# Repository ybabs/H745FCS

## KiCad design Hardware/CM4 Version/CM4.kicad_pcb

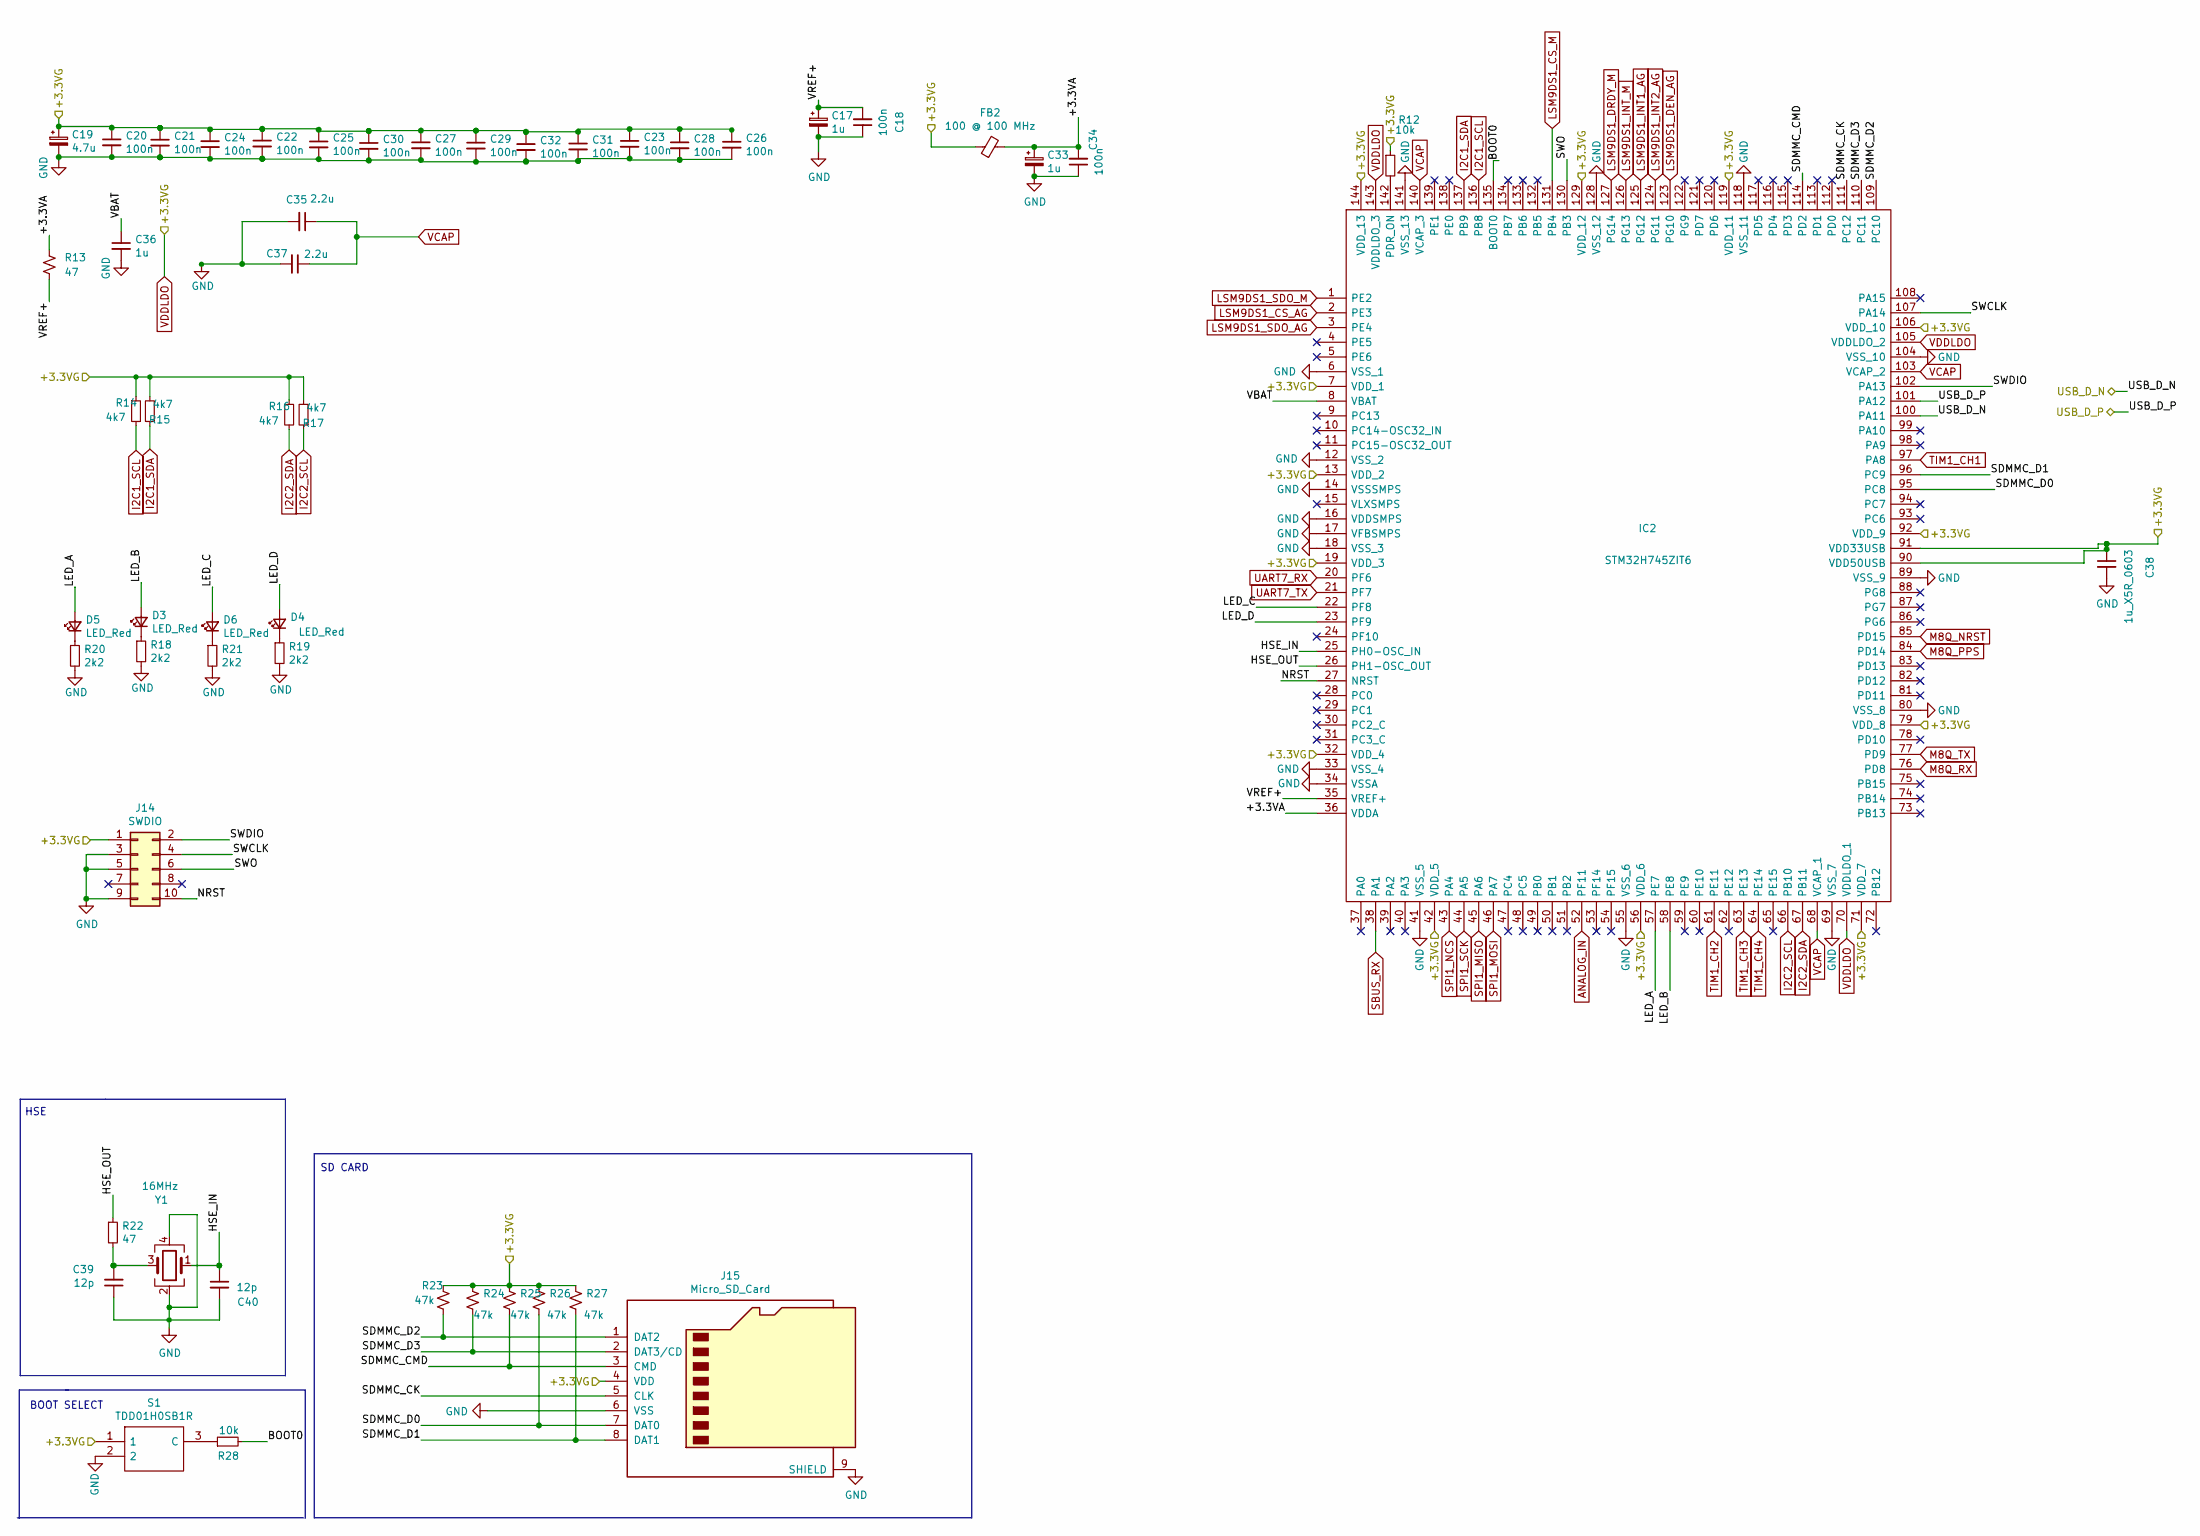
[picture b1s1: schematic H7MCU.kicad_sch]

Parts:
C17, C33: 1u; CP_EIA-3216-18_Kemet-A; Manufacturer_Part_Number TAJA105M016RNJ; LCSC Part # C7176
C18, C20, C21, C22, C23, C24, C25, C26, C27, C28, C29, C30, C31, C32, C34: 100n; C_0402_1005Metric; Digi-Key_PN 587-1226-2-ND
C19: 4.7u; CP_EIA-3216-18_Kemet-A; LCSC Part # C129235
C35, C37: 2.2u; C_0603_1608Metric; LCSC Part # C19666
C36: 1u; C_0402_1005Metric; Digi-Key_PN 587-1226-2-ND
C38: 1u_X5R_0603; C_0603_1608Metric; LCSC Part # C15849
C39, C40: 12p; C_0402_1005Metric; LCSC Part # C1547
D3, D4, D5, D6: LED_Red; LED_0603_1608Metric; LCSC Part # C72043
FB2: 100 @ 100 MHz; L_0603_1608Metric; Manufacturer_Part_Number MPZ1608S101ATAH0
IC2: STM32H745ZIT6; QFP50P2200X2200X160-144N; Manufacturer_Part_Number STM32H745ZIT6; Mouser Part Number 511-STM32H745ZIT6
J14: SWDIO; PinHeader_2x05_P1.27mm_Vertical
J15: Micro_SD_Card; microSD_HC_Hirose_DM3AT-SF-PEJM5; Manufacturer_Part_Number DM3AT-SF-PEJM5
R12, R28: 10k; R_0402_1005Metric; Digi-Key_PN RG10P10.0KDTR-ND
R13, R22: 47; R_0402_1005Metric; LCSC Part # C23182
R14, R15, R16, R17: 4k7; R_0402_1005Metric; LCSC Part # C23162
R18, R19, R20, R21: 2k2; R_0603_1608Metric; LCSC Part # C4190
R23, R24, R25, R26, R27: 47k; R_0402_1005Metric; Digi-Key_PN P47KDCTR-ND
S1: TDD01H0SB1R; SOT175P420X230-3N; Manufacturer_Part_Number TDD01H0SB1R; Mouser Part Number 611-TDD01H0SB1R
Y1: 16MHz; Crystal_SMD_3225-4Pin_3.2x2.5mm; Manufacturer_Part_Number X322516MLB4SI; LCSC Part # C13738

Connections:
/MCU/+3.3VA: C33.1, C34.2, FB2.2, IC2.36 (VDDA), R13.2
/MCU/BOOT0: IC2.135 (BOOT0), R28.2
/MCU/HSE_IN: C40.1, IC2.25 (PH0-OSC_IN), Y1.1
/MCU/HSE_OUT: IC2.26 (PH1-OSC_OUT), R22.1
/MCU/LED_A: D5.2 (A), IC2.57 (PE7)
/MCU/LED_B: D3.2 (A), IC2.58 (PE8)
/MCU/LED_C: D6.2 (A), IC2.22 (PF8)
/MCU/LED_D: D4.2 (A), IC2.23 (PF9)
/MCU/NRST: IC2.27 (NRST), J14.10
/MCU/SDMMC_CK: IC2.111 (PC12), J15.5 (CLK)
/MCU/SDMMC_CMD: IC2.114 (PD2), J15.3 (CMD), R25.1
/MCU/SDMMC_D0: IC2.95 (PC8), J15.7 (DAT0), R26.1
/MCU/SDMMC_D1: IC2.96 (PC9), J15.8 (DAT1), R27.1
/MCU/SDMMC_D2: IC2.109 (PC10), J15.1 (DAT2), R23.1
/MCU/SDMMC_D3: IC2.110 (PC11), J15.2 (DAT3/CD), R24.1
/MCU/SWCLK: IC2.107 (PA14), J14.4
/MCU/SWDIO: IC2.102 (PA13), J14.2
/MCU/SWO: IC2.130 (PB3), J14.6
/MCU/VBAT: C36.1, IC2.8 (VBAT)
/MCU/VREF+: C17.1, C18.2, IC2.35 (VREF+), R13.1
GND: C17.2, C18.1, C19.2, C20.2, C21.2, C22.2, C23.2, C24.2, C25.2, C26.2, C27.2, C28.2, C29.2, C30.2, C31.2, C32.2, C33.2, C34.1, C35.2, C36.2, C37.2, C38.2, C39.1, C40.2, IC2.6 (VSS_1), IC2.12 (VSS_2), IC2.14 (VSSSMPS), IC2.16 (VDDSMPS), IC2.17 (VFBSMPS), IC2.18 (VSS_3), IC2.33 (VSS_4), IC2.34 (VSSA), IC2.41 (VSS_5), IC2.55 (VSS_6), IC2.69 (VSS_7), IC2.80 (VSS_8), IC2.89 (VSS_9), IC2.104 (VSS_10), IC2.118 (VSS_11), IC2.128 (VSS_12), IC2.141 (VSS_13), J14.3, J14.5, J14.9, J15.6 (VSS), J15.9 (SHIELD), R18.2, R19.2, R20.2, R21.2, S1.2, Y1.2, Y1.4; also elsewhere on the board
I2C1_SCL: IC2.136 (PB8), R14.2; also elsewhere on the board
I2C1_SDA: IC2.137 (PB9), R15.1; also elsewhere on the board
I2C2_SCL: IC2.66 (PB10), R17.1; also elsewhere on the board
I2C2_SDA: IC2.67 (PB11), R16.2; also elsewhere on the board
unnamed: C39.2, R22.2, Y1.3
unnamed: D3.1 (K), R18.1
unnamed: D4.1 (K), R19.1
unnamed: D5.1 (K), R20.1
unnamed: D6.1 (K), R21.1
unnamed: IC2.142 (PDR_ON), R12.2
unnamed: R28.1, S1.3 (C)
VCAP: C35.1, C37.1, IC2.68 (VCAP_1), IC2.103 (VCAP_2), IC2.140 (VCAP_3)
VDDLDO: C19.1, C20.1, C21.1, C22.1, C23.1, C24.1, C25.1, C26.1, C27.1, C28.1, C29.1, C30.1, C31.1, C32.1, C38.1, FB2.1, IC2.7 (VDD_1), IC2.13 (VDD_2), IC2.19 (VDD_3), IC2.32 (VDD_4), IC2.42 (VDD_5), IC2.56 (VDD_6), IC2.70 (VDDLDO_1), IC2.71 (VDD_7), IC2.79 (VDD_8), IC2.90 (VDD50USB), IC2.91 (VDD33USB), IC2.92 (VDD_9), IC2.105 (VDDLDO_2), IC2.106 (VDD_10), IC2.119 (VDD_11), IC2.129 (VDD_12), IC2.143 (VDDLDO_3), IC2.144 (VDD_13), J14.1, J15.4 (VDD), R12.1, R14.1, R15.2, R16.1, R17.2, R23.2, R24.2, R25.2, R26.2, R27.2, S1.1; also elsewhere on the board

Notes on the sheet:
SD CARD
HSE
BOOT SELECT

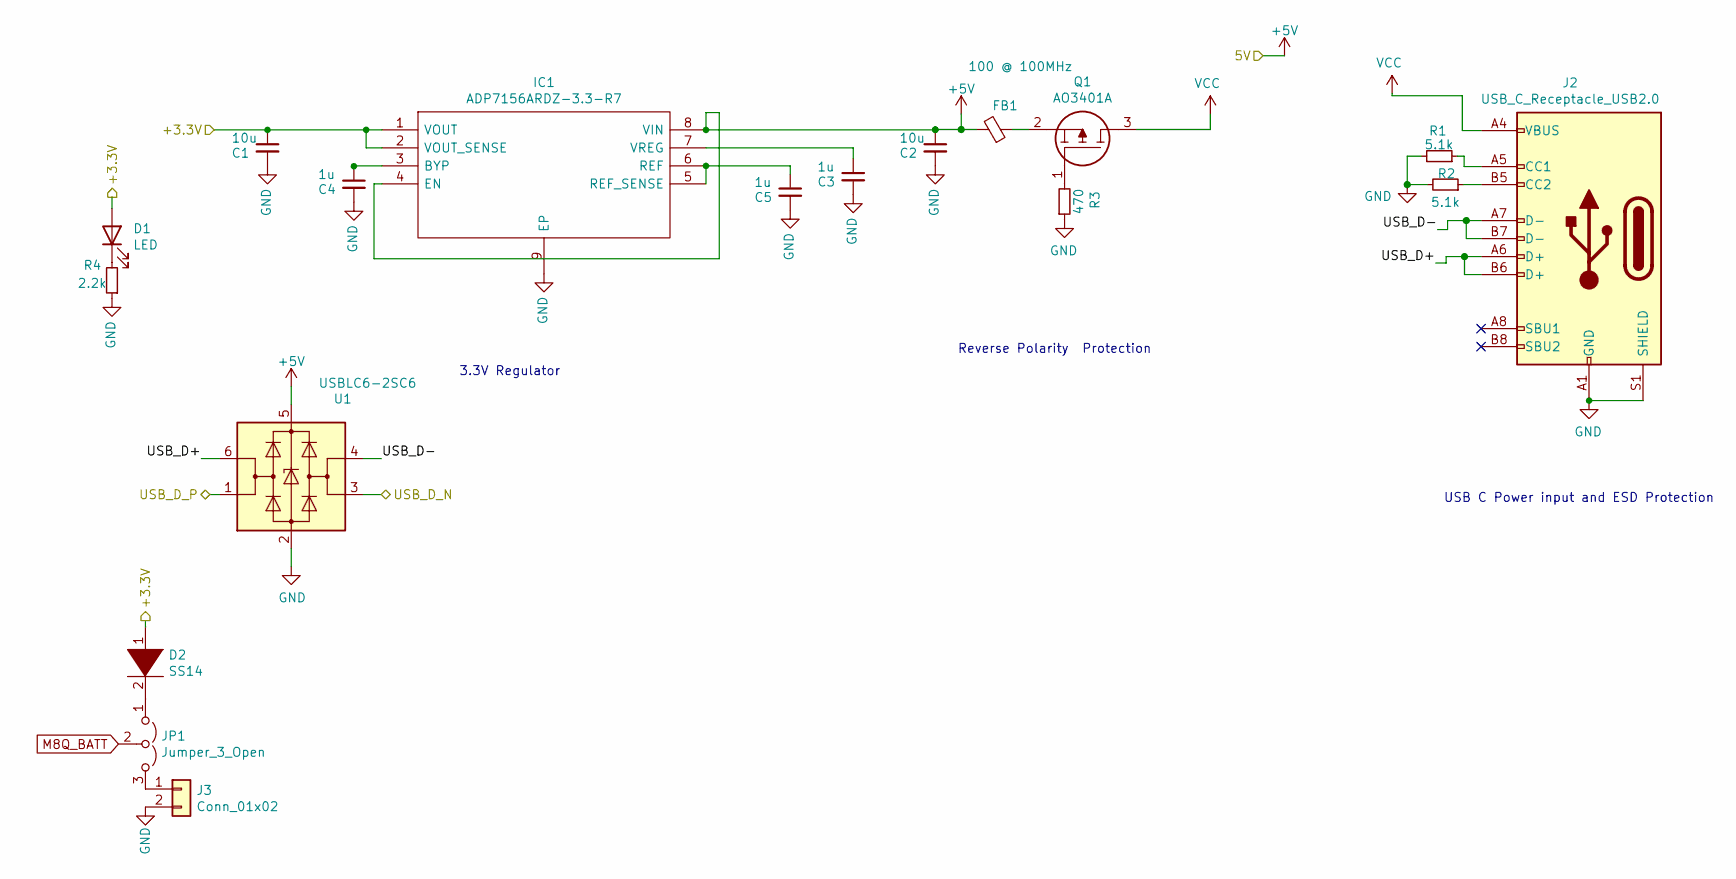
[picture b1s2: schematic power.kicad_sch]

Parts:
C1, C2: 10u; C_0603_1608Metric; LCSC Part # C19702
C3, C4, C5: 1u; C_0603_1608Metric; LCSC Part # C15849
D1: LED; LED_0603_1608Metric; LCSC Part # C72043
D2: SS14; D_SMA; LCSC Part # C111631
FB1: 100 @ 100MHz; L_0603_1608Metric; Manufacturer_Part_Number BLM21PG600SH1D
IC1: ADP7156ARDZ-3.3-R7; SOIC127P600X175-9N; Manufacturer_Part_Number ADP7156ARDZ-3.3-R7; Mouser Part Number 584-ADP7156ARDZ3.3R7
J2: USB_C_Receptacle_USB2.0; USB_C_Receptacle_HRO_TYPE-C-31-M-12; Manufacturer_Part_Number TYPE-C-31-M-12; LCSC Part # C165948
J3: Conn_01x02; Molex_PicoBlade_53261-0271_1x02-1MP_P1.25mm_Horizontal; Manufacturer_Part_Number 0532610271; Digi-Key_PN WM7620TR-ND
JP1: Jumper_3_Open; SolderJumper-3_P1.3mm_Open_RoundedPad1.0x1.5mm
Q1: AO3401A; SOT95P280X125-3N; Manufacturer_Part_Number AO3401A
R1, R2: 5.1k; R_1206_3216Metric; LCSC Part # C26033
R3: 470; R_1206_3216Metric; LCSC Part # C26033
R4: 2.2k; R_0603_1608Metric; LCSC Part # C4190
U1: USBLC6-2SC6; SOT-23-6; Manufacturer_Part_Number USBLC6-2SC6; LCSC Part # C7519

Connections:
+5V: C2.1, FB1.2, IC1.4 (EN), IC1.8 (VIN), U1.5 (VBUS); also elsewhere on the board
/Power/USB_D+: J2.A6 (D+), J2.B6 (D+), U1.6 (I/O1)
/Power/USB_D-: J2.A7 (D-), J2.B7 (D-), U1.4 (I/O2)
/Power/USB_D_N: U1.3 (I/O2)
/Power/USB_D_P: U1.1 (I/O1)
GND: C1.2, C2.2, C3.2, C4.2, C5.2, IC1.9 (EP), J2.A1 (GND), J2.A12 (GND), J2.B1 (GND), J2.B12 (GND), J2.S1 (SHIELD), J3.2, R1.2, R2.2, R3.1, R4.1, U1.2 (GND); also elsewhere on the board
M8Q_BATT: JP1.2 (C)
unnamed: C3.1, IC1.7 (VREG)
unnamed: C4.1, IC1.3 (BYP)
unnamed: C5.1, IC1.5 (REF_SENSE), IC1.6 (REF)
unnamed: D1.1 (K), R4.2
unnamed: D2.2 (A), JP1.1 (A)
unnamed: FB1.1, Q1.2
unnamed: J2.A5 (CC1), R1.1
unnamed: J2.B5 (CC2), R2.1
unnamed: J3.1, JP1.3 (B)
unnamed: Q1.1, R3.2
VCC: J2.A4 (VBUS), J2.A9 (VBUS), J2.B4 (VBUS), J2.B9 (VBUS), Q1.3
VDDLDO: C1.1, D1.2 (A), D2.1 (K), IC1.1 (VOUT), IC1.2 (VOUT_SENSE); also elsewhere on the board

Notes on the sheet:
3.3V Regulator
Reverse Polarity Protection
USB C Power input and ESD Protection

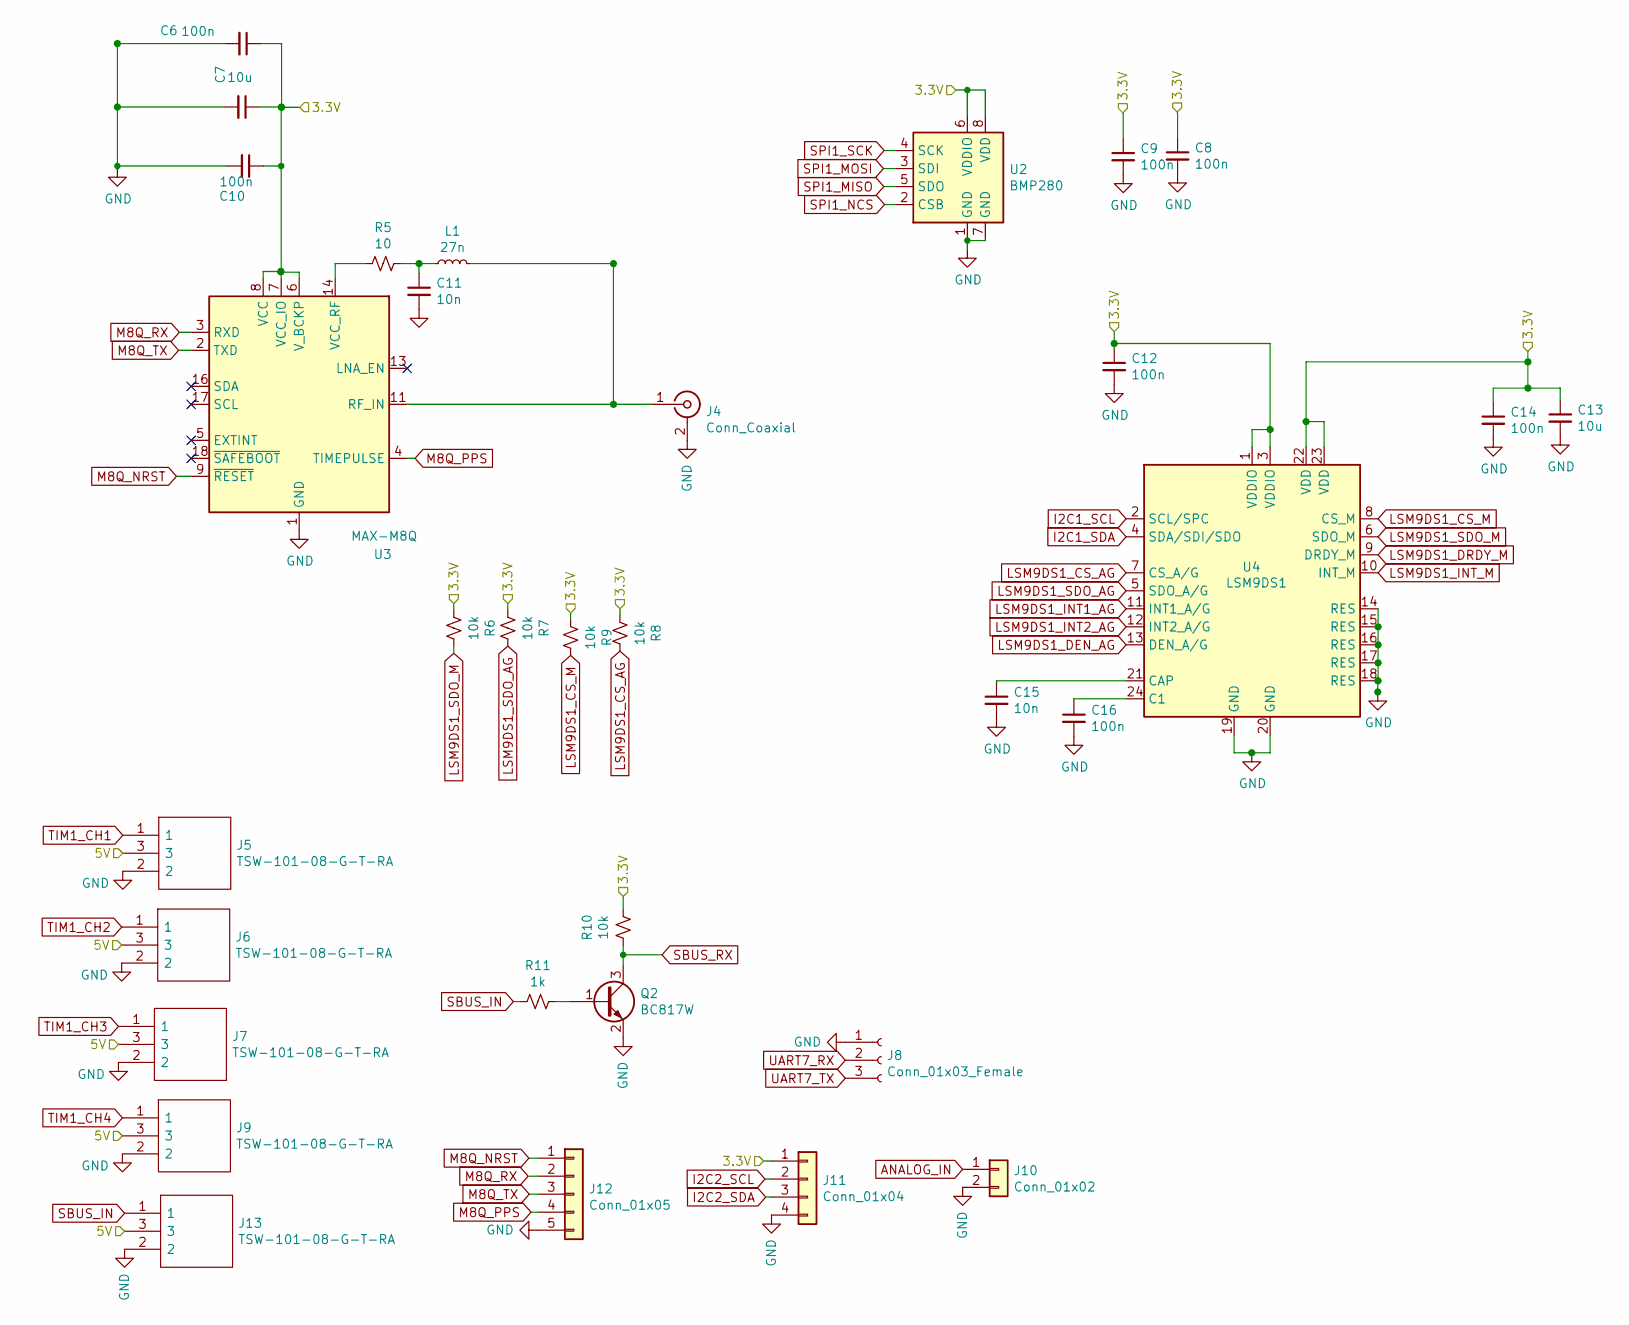
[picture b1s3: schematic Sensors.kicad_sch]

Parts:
C6, C8, C9, C10, C12, C14, C16: 100n; C_0402_1005Metric; Digi-Key_PN 587-1226-2-ND
C7: 10u; C_0603_1608Metric; LCSC Part # C15849
C11, C15: 10n; C_0402_1005Metric; LCSC Part # C15195
C13: 10u; C_0603_1608Metric; LCSC Part # C19702
J4: Conn_Coaxial; BWIPX-1-001E
J5, J6, J7, J9, J13: TSW-101-08-G-T-RA; HDRRA3W64P254_3X1_254X254X810P; Mouser Part Number 200-HTSW10108GTRA
J8: Conn_01x03_Female; PinHeader_1x03_P2.54mm_Vertical
J10: Conn_01x02; Molex_PicoBlade_53048-0210_1x02_P1.25mm_Horizontal; Manufacturer_Part_Number 0530480210; Digi-Key_PN WM1742-ND
J11: Conn_01x04; Molex_PicoBlade_53261-0471_1x04-1MP_P1.25mm_Horizontal; Manufacturer_Part_Number 0532610471; Digi-Key_PN WM7622TR-ND
J12: Conn_01x05; Molex_PicoBlade_53047-0510_1x05_P1.25mm_Vertical
L1: 27n; L_0402_1005Metric_Pad0.77x0.64mm_HandSolder; Manufacturer_Part_Number LQG15HS27NJ02D; LCSC Part # C18830
Q2: BC817W; SOT-323_SC-70; Digi-Key_PN 1727-4843-2-ND
R5: 10; R_0402_1005Metric; LCSC Part # C22859
R6, R7, R8, R9, R10: 10k; R_0402_1005Metric; Digi-Key_PN RG10P10.0KDTR-ND
R11: 1k; R_0402_1005Metric; LCSC Part # C21190
U2: BMP280; Bosch_LGA-8_2x2.5mm_P0.65mm_ClockwisePinNumbering; Manufacturer_Part_Number 314030010
U3: MAX-M8Q; ublox_MAX
U4: LSM9DS1; LGA-24L_3x3.5mm_P0.43mm; Digi-Key_PN 497-14946-2-ND

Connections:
ANALOG_IN: J10.1
GND: C6.2, C7.2, C8.2, C9.2, C10.2, C11.2, C12.2, C13.2, C14.2, C15.2, C16.2, J4.2 (Ext), J5.2, J6.2, J7.2, J8.1, J9.2, J10.2, J11.4, J12.5, J13.2, Q2.2 (E), U2.1 (GND), U2.7 (GND), U3.1 (GND), U3.10 (GND), U3.12 (GND), U4.14 (RES), U4.15 (RES), U4.16 (RES), U4.17 (RES), U4.18 (RES), U4.19 (GND), U4.20 (GND); also elsewhere on the board
I2C1_SCL: U4.2 (SCL/SPC); also elsewhere on the board
I2C1_SDA: U4.4 (SDA/SDI/SDO); also elsewhere on the board
I2C2_SCL: J11.2; also elsewhere on the board
I2C2_SDA: J11.3; also elsewhere on the board
LSM9DS1_CS_AG: R8.2, U4.7 (CS_A/G)
LSM9DS1_CS_M: R9.2, U4.8 (CS_M)
LSM9DS1_DEN_AG: U4.13 (DEN_A/G)
LSM9DS1_DRDY_M: U4.9 (DRDY_M)
LSM9DS1_INT1_AG: U4.11 (INT1_A/G)
LSM9DS1_INT2_AG: U4.12 (INT2_A/G)
LSM9DS1_INT_M: U4.10 (INT_M)
LSM9DS1_SDO_AG: R7.2, U4.5 (SDO_A/G)
LSM9DS1_SDO_M: R6.2, U4.6 (SDO_M)
M8Q_NRST: J12.1, U3.9 (~RESET)
M8Q_PPS: J12.4, U3.4 (TIMEPULSE)
M8Q_RX: J12.2, U3.3 (RXD)
M8Q_TX: J12.3, U3.2 (TXD)
unnamed: C11.1, L1.1, R5.2
unnamed: C15.1, U4.21 (CAP)
unnamed: C16.1, U4.24 (C1)
unnamed: J4.1 (In), L1.2, U3.11 (RF_IN)
unnamed: J5.3, J6.3, J7.3, J9.3, J13.3
unnamed: Q2.1 (B), R11.2
unnamed: R5.1, U3.14 (VCC_RF)
SBUS_IN: J13.1, R11.1
SBUS_RX: Q2.3 (C), R10.1
SPI1_MISO: U2.5 (SDO)
SPI1_MOSI: U2.3 (SDI)
SPI1_NCS: U2.2 (CSB)
SPI1_SCK: U2.4 (SCK)
UART7_RX: J8.2
UART7_TX: J8.3
VDDLDO: C6.1, C7.1, C8.1, C9.1, C10.1, C12.1, C13.1, C14.1, J11.1, R6.1, R7.1, R8.1, R9.1, R10.2, U2.6 (VDDIO), U2.8 (VDD), U3.6 (V_BCKP), U3.7 (VCC_IO), U3.8 (VCC), U4.1 (VDDIO), U4.3 (VDDIO), U4.22 (VDD), U4.23 (VDD); also elsewhere on the board

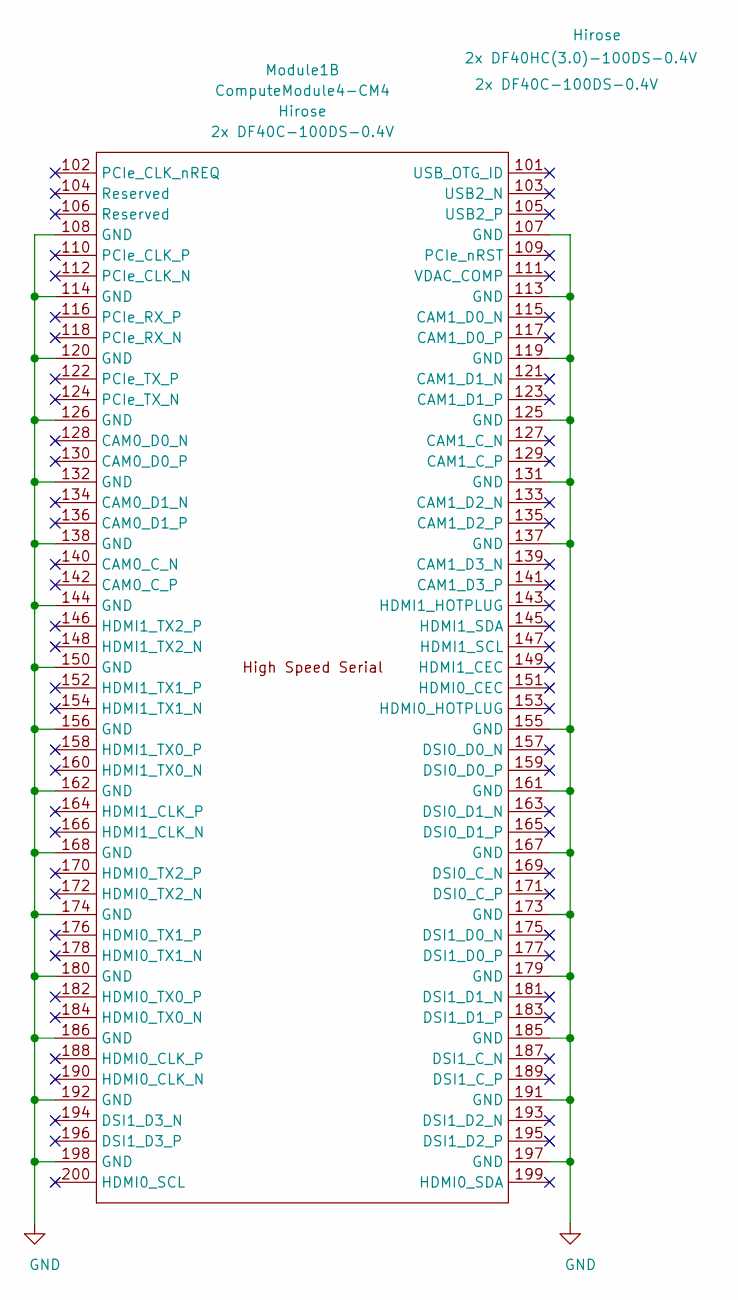
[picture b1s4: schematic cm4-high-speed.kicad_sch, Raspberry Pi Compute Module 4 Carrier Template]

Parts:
Module1: ComputeModule4-CM4; Raspberry-Pi-4-Compute-Module; MPN 2x DF40C-100DS-0.4V; Digi-Key_PN 2x H124602TR-ND

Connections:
GND: Module1.107 (GND), Module1.108 (GND), Module1.113 (GND), Module1.114 (GND), Module1.119 (GND), Module1.120 (GND), Module1.125 (GND), Module1.126 (GND), Module1.131 (GND), Module1.132 (GND), Module1.137 (GND), Module1.138 (GND), Module1.144 (GND), Module1.150 (GND), Module1.155 (GND), Module1.156 (GND), Module1.161 (GND), Module1.162 (GND), Module1.167 (GND), Module1.168 (GND), Module1.173 (GND), Module1.174 (GND), Module1.179 (GND), Module1.180 (GND), Module1.185 (GND), Module1.186 (GND), Module1.191 (GND), Module1.192 (GND), Module1.197 (GND), Module1.198 (GND); also elsewhere on the board

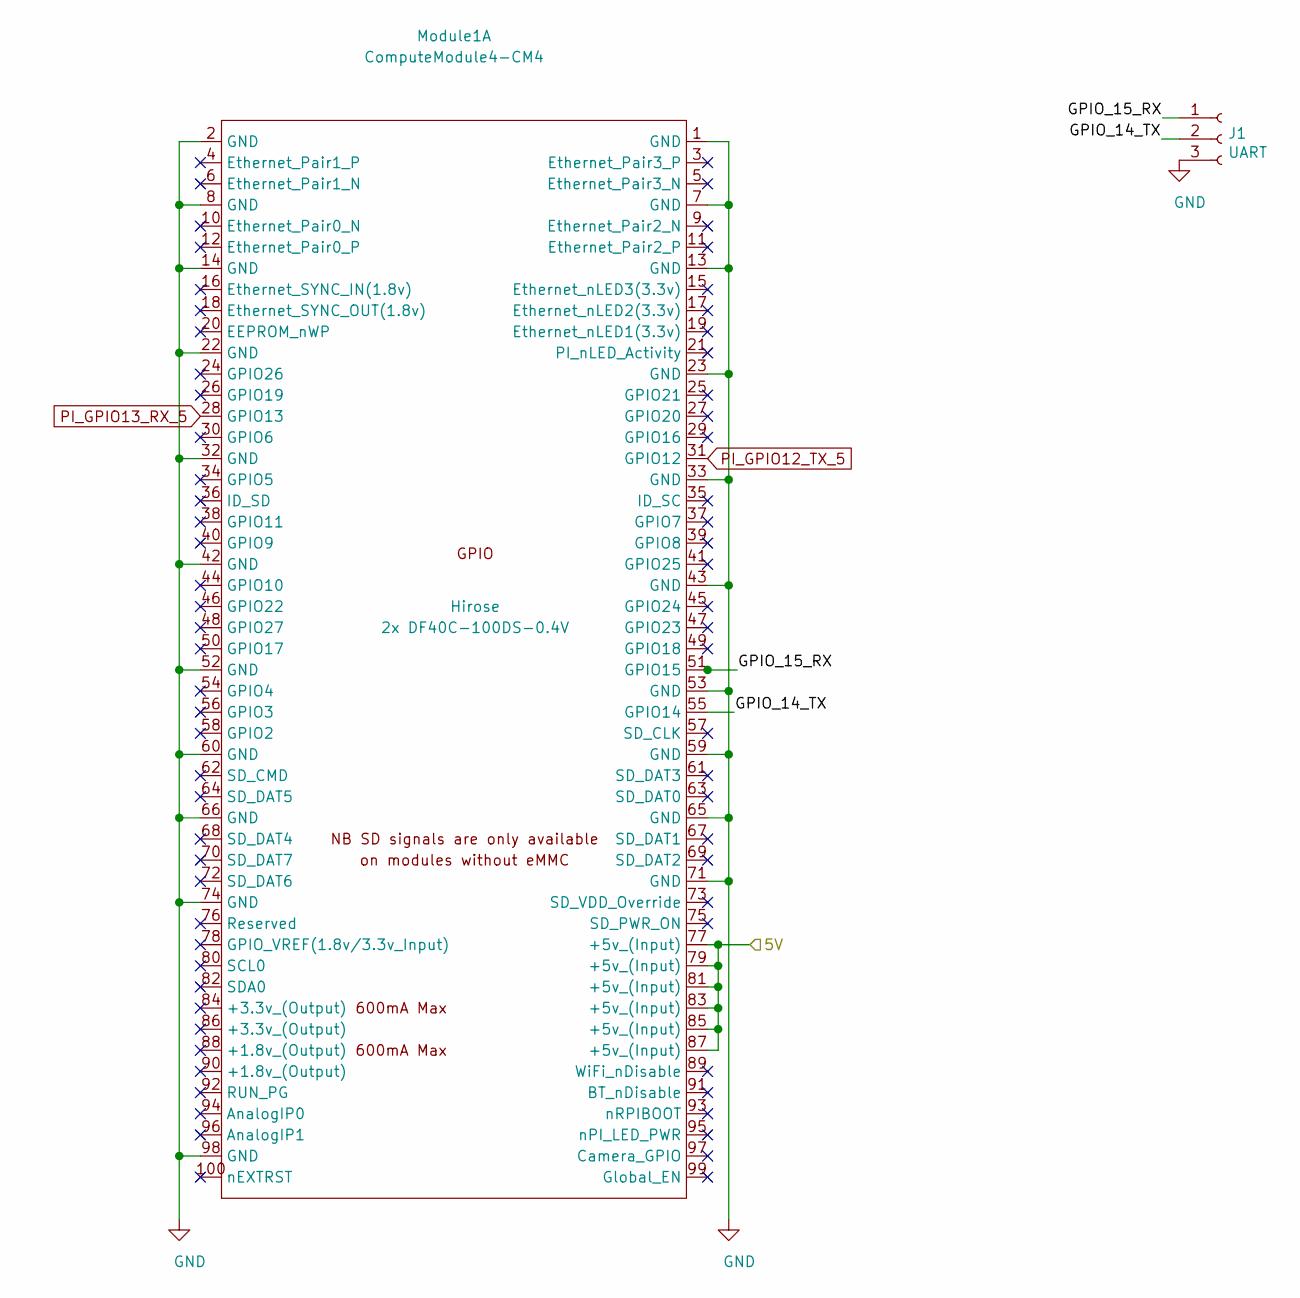
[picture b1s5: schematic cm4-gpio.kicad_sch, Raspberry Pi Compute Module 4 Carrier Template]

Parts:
J1: UART; Molex_PicoBlade_53261-0371_1x03-1MP_P1.25mm_Horizontal; Manufacturer_Part_Number 0532610371; Digi-Key_PN WM7621TR-ND
Module1: ComputeModule4-CM4; Raspberry-Pi-4-Compute-Module; MPN 2x DF40C-100DS-0.4V; Digi-Key_PN 2x H124602TR-ND

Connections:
+5V: Module1.77 (+5v_(Input)), Module1.79 (+5v_(Input)), Module1.81 (+5v_(Input)), Module1.83 (+5v_(Input)), Module1.85 (+5v_(Input)), Module1.87 (+5v_(Input)); also elsewhere on the board
/CM4 GPIO/GPIO_14_TX: J1.2, Module1.55 (GPIO14)
/CM4 GPIO/GPIO_15_RX: J1.1, Module1.51 (GPIO15)
GND: J1.3, Module1.1 (GND), Module1.2 (GND), Module1.7 (GND), Module1.8 (GND), Module1.13 (GND), Module1.14 (GND), Module1.22 (GND), Module1.23 (GND), Module1.32 (GND), Module1.33 (GND), Module1.42 (GND), Module1.43 (GND), Module1.52 (GND), Module1.53 (GND), Module1.59 (GND), Module1.60 (GND), Module1.65 (GND), Module1.66 (GND), Module1.71 (GND), Module1.74 (GND), Module1.98 (GND); also elsewhere on the board
PI_GPIO12_TX_5: Module1.31 (GPIO12)
PI_GPIO13_RX_5: Module1.28 (GPIO13)

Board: 4 copper layers, 94 parts (2 on the bottom side), 46 nets, no tracks yet.

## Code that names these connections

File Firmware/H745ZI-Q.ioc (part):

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PF7.GPIOParameters=PinAttribute
PE11.GPIOParameters=PinAttribute
PB10.Mode=I2C
PH0-OSC_IN\ (PH0).PinAttribute=CortexM7
PC12.Signal=SDMMC1_CK
PA6.PinAttribute=CortexM4
PA5.PinAttribute=CortexM4
PD2.GPIOParameters=PinAttribute
PG14.GPIOParameters=GPIO_Label,PinAttribute
PB3\ (JTDO/TRACESWO).GPIOParameters=PinAttribute
PG13.Signal=GPXTI13
RCC.SYSCLKSource=RCC_SYSCLKSOURCE_PLLCLK
PB8.PinAttribute=CortexM4
PA14\ (JTCK/SWCLK).Signal=DEBUG_JTCK-SWCLK
PD15.GPIOParameters=GPIO_Label,PinAttribute
PF7.Signal=UART7_TX
PD8.Signal=USART3_TX
PC8.PinAttribute=CortexM4
PA1.GPIOParameters=GPIO_Label,PinAttribute
PG12.GPIOParameters=GPIO_Label,PinAttribute
PD8.PinAttribute=CortexM4
PE4.GPIO_Label=LSM9DS1_SDO_AG
PC9.Mode=SD_4_bits_Wide_bus
PE2.Signal=GPIO_Output
PA8.Signal=S_TIM1_CH1
PA14\ (JTCK/SWCLK).Mode=Trace_Asynchronous_SW
PC8.GPIOParameters=PinAttribute
PA7.PinAttribute=CortexM4
Mcu.Package=LQFP144
PB9.Signal=I2C1_SDA
PF8.GPIOParameters=GPIO_Label,PinAttribute
PG13.GPIOParameters=GPIO_Label,PinAttribute
PA5.GPIOParameters=PinAttribute
PC11.Mode=SD_4_bits_Wide_bus
PB10.GPIOParameters=PinAttribute
PH0-OSC_IN\ (PH0).Mode=HSE-External-Oscillator
PA4.GPIO_Label=SPI1_NCS
PD15.Signal=GPIO_Input
PG10.PinAttribute=Free
PA5.Mode=Full_Duplex_Master
PG12.Signal=GPXTI12
PA6.GPIOParameters=PinAttribute
PG12.PinAttribute=CortexM4
PA1.PinAttribute=Free
PF9.PinAttribute=Free
PE8.PinAttribute=Free
PC11.GPIOParameters=PinAttribute
PG13.GPIO_Label=LSM9DS1_INT_M
PG10.Signal=GPIO_Output
PG13.PinAttribute=CortexM4
PF8.GPIO_Label=LED_C
PB4\ (NJTRST).PinAttribute=Free
PF11.Mode=IN2-Single-Ended
PA12.PinAttribute=CortexM4
PB11.Mode=I2C
PE8.GPIO_Label=LED_B
PB11.GPIOParameters=PinAttribute
PD8.Mode=Asynchronous
PB10.Signal=I2C2_SCL
PA5.Signal=SPI1_SCK
PE13.GPIOParameters=PinAttribute
PC12.Mode=SD_4_bits_Wide_bus
PG11.PinAttribute=CortexM4
PB9.PinAttribute=CortexM4
PE14.Signal=S_TIM1_CH4
PA11.PinAttribute=CortexM4
PE8.Signal=GPIO_Output
PA1.GPIO_Label=SBUS_RX
PC10.GPIOParameters=PinAttribute
PG14.GPIO_Label=LSM9DS1_DRDY_M
PC9.GPIOParameters=PinAttribute
PF9.GPIOParameters=GPIO_Label,PinAttribute
PB3\ (JTDO/TRACESWO).PinAttribute=CortexM7
PE2.PinAttribute=Free
PC8.Mode=SD_4_bits_Wide_bus
PA4.Signal=GPIO_Output
PD14.GPIOParameters=GPIO_Label,PinAttribute
PA8.PinAttribute=CortexM4
PA11.Signal=USB_OTG_FS_DM
PD9.PinAttribute=CortexM4
PF6.Mode=Asynchronous
PF9.Signal=GPIO_Output
PA14\ (JTCK/SWCLK).PinAttribute=CortexM7
PG12.ContextOwner=CortexM4
PB3\ (JTDO/TRACESWO).Mode=Trace_Asynchronous_SW
PB8.Mode=I2C
PD15.PinAttribute=Free
PE3.Signal=GPIO_Output
PC9.PinAttribute=CortexM4
PB4\ (NJTRST).GPIO_Label=LSM9DS1_CS_M
PE14.PinAttribute=CortexM4
PD2.Signal=SDMMC1_CMD
PA7.GPIOParameters=PinAttribute
PG10.GPIO_Label=LSM9DS1_DEN_AG
PA13\ (JTMS/SWDIO).Signal=DEBUG_JTMS-SWDIO
PD2.PinAttribute=CortexM4
PA6.Mode=Full_Duplex_Master
PA14\ (JTCK/SWCLK).GPIOParameters=PinAttribute
PB10.PinAttribute=CortexM4
Mcu.UserName=STM32H745ZITx
PD9.GPIOParameters=PinAttribute
PG13.ContextOwner=CortexM4
PH0-OSC_IN\ (PH0).Signal=RCC_OSC_IN
PC10.Signal=SDMMC1_D2
PA12.GPIOParameters=PinAttribute
PA11.GPIOParameters=PinAttribute
PA11.Mode=Device_Only
PC12.PinAttribute=CortexM4
PB11.Signal=I2C2_SDA
PD9.Mode=Asynchronous
PE3.PinAttribute=Free
PC11.PinAttribute=CortexM4
PE4.PinAttribute=Free
PG11.Signal=GPXTI11
PB11.PinAttribute=CortexM4
PA12.Signal=USB_OTG_FS_DP
PE4.GPIOParameters=GPIO_Label,PinAttribute
PD8.GPIOParameters=PinAttribute
PE13.PinAttribute=CortexM4
PA8.GPIOParameters=PinAttribute
PH1-OSC_OUT\ (PH1).Mode=HSE-External-Oscillator
RCC.HSE_VALUE=16000000
PG14.PinAttribute=Free
PA13\ (JTMS/SWDIO).PinAttribute=CortexM7
PE13.Signal=S_TIM1_CH3
PF11.Signal=ADC1_INP2
PD14.PinAttribute=Free
PE3.GPIOParameters=GPIO_Label,PinAttribute
PG11.ContextOwner=CortexM4
PF11.GPIOParameters=PinAttribute
PF7.PinAttribute=CortexM7
PE4.Signal=GPIO_Output
PF8.PinAttribute=Free
PA6.Signal=SPI1_MISO
PC10.PinAttribute=CortexM4
PF8.Signal=GPIO_Output
PG11.GPIO_Label=LSM9DS1_INT2_AG
PE7.Signal=GPIO_Output
PF11.PinAttribute=CortexM4
PE2.GPIO_Label=LSM9DS1_SDO_M
PH1-OSC_OUT\ (PH1).PinAttribute=CortexM7
PE8.GPIOParameters=GPIO_Label,PinAttribute
PB8.GPIOParameters=PinAttribute
PD15.GPIO_Label=M8Q_NRST
PA7.Mode=Full_Duplex_Master
PA13\ (JTMS/SWDIO).Mode=Trace_Asynchronous_SW
PE14.GPIOParameters=PinAttribute
PC11.Signal=SDMMC1_D3
PC8.Signal=SDMMC1_D0
PC10.Mode=SD_4_bits_Wide_bus
PD9.Signal=USART3_RX
PE7.PinAttribute=Free
boardIOC=true
PA13\ (JTMS/SWDIO).GPIOParameters=PinAttribute
PH1-OSC_OUT\ (PH1).Signal=RCC_OSC_OUT
PB9.GPIOParameters=PinAttribute
PC12.GPIOParameters=PinAttribute
PF7.Mode=Asynchronous
PB4\ (NJTRST).GPIOParameters=GPIO_Label,PinAttribute
PH1-OSC_OUT\ (PH1).GPIOParameters=PinAttribute
PF6.Signal=UART7_RX
PB3\ (JTDO/TRACESWO).Signal=DEBUG_JTDO-SWO
PE7.GPIOParameters=GPIO_Label,PinAttribute
PE11.PinAttribute=CortexM4
PB9.Mode=I2C
PE2.GPIOParameters=GPIO_Label,PinAttribute
PG10.GPIOParameters=GPIO_Label,PinAttribute
PF9.GPIO_Label=LED_D
PE11.Signal=S_TIM1_CH2
PA1.Signal=GPIO_Output
PD2.Mode=SD_4_bits_Wide_bus
PG14.Signal=GPIO_Output
board=NUCLEO-H745ZI-Q
PD14.GPIO_Label=M8Q_PPS
PA4.GPIOParameters=GPIO_Label,PinAttribute
Mcu.Name=STM32H745ZITx
PA4.PinAttribute=Free
PE7.GPIO_Label=LED_A
PD14.Signal=GPIO_Output
RCC.SYSCLKFreq_VALUE=480000000
PA12.Mode=Device_Only
PF6.GPIOParameters=PinAttribute
PF6.PinAttribute=CortexM7
PG12.GPIO_Label=LSM9DS1_INT_AG
PB8.Signal=I2C1_SCL
PE3.GPIO_Label=LSM9DS1_CS_AG
PC9.Signal=SDMMC1_D1
PG11.GPIOParameters=GPIO_Label,PinAttribute
PH0-OSC_IN\ (PH0).GPIOParameters=PinAttribute
PA7.Signal=SPI1_MOSI
PB4\ (NJTRST).Signal=GPIO_Output

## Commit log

2020-08-02 Added Motor Driver
2020-08-12 Added Accelerometer driver
2020-08-13 Added Mag and Tempo
2020-08-19 Added Gyro driver
2020-08-24 Added barometer
2020-09-02 Added GPS Parser
2020-09-29 Added GPS Driver
2020-09-30 Added Mag and Acc Tasks
2021-01-16 Update object file
2021-04-05 Merged Hardware files with firmware
2021-04-05 Merged Files
2021-07-06 Set initial cUbeMX Cconfig. Fixed Clock and GPIO bug
2021-07-07 Added GPS driver. Need to figure out why pressure sensor doesn't work
2021-08-04 Added Baremetal firmware
2021-08-16 Added GPS Driver for Baremetal
2021-08-19 Fixed Dualcore Debug issue and changed IMU to bloc king function
2021-10-01 Sync changes
2021-10-06 Add HSEM Data Transfer from M4 to M7
2021-11-05 Setup other peripherals using CubeMX
2021-11-05 Setup USB CDC
2021-11-06 USB bringup
2021-11-15 Added RingBuf Implementation
2021-11-15 Added FIR
2021-11-16 Added RC Filter
2021-12-30 Refactoring of BMP80 Class
2021-12-30 Refactor IMU CODE
2022-01-02 Refactor GPS Driver
2022-01-03 Format Edited lines
2022-01-04 Changed BMP280 Driver to blocking
2022-01-04 Finished M4 Drivers
2022-01-18 Start SBUS support
2022-01-23 update gitignore
2022-01-23 Remove Ignored files
2022-01-23 Renove Filters folder
2022-01-23 Remove CM4-Backups
2022-01-23 Remove .zips
2022-01-24 Add SBUS support
2022-02-01 Add source file for state estimation
2022-02-16 Add Madgwick and Mahony Filter
2022-03-08 Change SBUS UART to use IDLE line detection
2022-03-13 Cleanup unused files
2022-03-13 Add LED heartbeat
2022-04-09 Fix errors with update to Cube 1.9.0 fcommon issue
2022-04-09 Add LPF Imu data
2022-04-16 Add LP filter to IMU
2022-04-19 Add QT Base GUI
2022-04-21 Add VCP Uart Interface
2022-04-22 Send Sensor data over USB using new structure
2022-05-26 Add UART Frame Parser
2022-08-25 New gitignore Resync
2022-09-16 New Local Branch
2022-10-11 Add calibration for accelerometer
2022-10-11 Add Gyro Calibration
2022-10-12 Add calibration call. Need to test when computer is setup
2022-10-12 Add Sbus protocol back in
2022-10-12 Add fix for missing initiliaser warning in SystemClockCOnfig
2022-10-19 Add Serializer
2022-10-19 Add Eigen Library to project
2022-10-26 Use HSEM to communicate between CM4 and CM7
2022-11-16 branch to see why data repeating
2022-12-18 SOlvce slow transmit bug
2023-02-28 Update to send GPS and barometer data over USB CDC

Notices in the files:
Hardware/CM4 Version/CM4.kicad_pcb:
creativecommons.org/licenses/by/4.0
License: CC BY 4.0
Hardware/CM4 Version/cm4-gpio.kicad_sch:
creativecommons.org/licenses/by-sa/4.0
